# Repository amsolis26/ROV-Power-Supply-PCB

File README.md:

# ROV Power Supply PCB

## Problem
A common laptop power supply provides a much higher voltage than what the electronics in my ROV are rated for. To solve this issue, I needed to design a PCB that can fit into the 3-Inch Diameter Housing of my ROV to safely step down the voltage and power my onboard electronics.

## Approach
- Select DC/DC converter suited for the voltage conversion **(48V to 8V)** I need to power the ROV
- Design a schematic & PCB Layout using KiCAD
- Send out files for PCB manufacturing
- Order & Solder components together
- Use Desk Power supply to test if the output meets desired Voltage

## Results
The PCB delivers an output **~8V**, successfully powering onboard electronics.

## Tools
- **KiCAD** (Schematic & PCB Design)
- **PCB Way** (PCB Manufacturing)
- **DigiKey** (Part Lookup & Ordering)

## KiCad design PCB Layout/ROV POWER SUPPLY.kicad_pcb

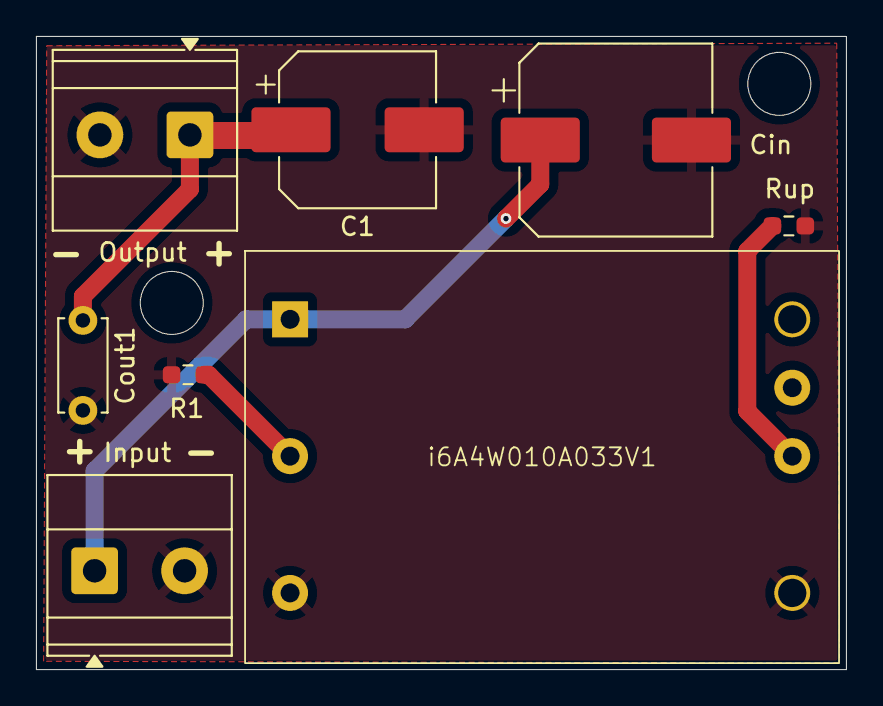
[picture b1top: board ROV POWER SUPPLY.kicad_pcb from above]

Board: 2 copper layers, 45.0 x 35.2 mm, 8 parts (0 on the bottom side), 5 nets.

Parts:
C1: 100uF; CP_Elec_8x10.5
Cin: 100uF; CP_Elec_10x12.5
Cout1: 0.1uF; C_Disc_D5.0mm_W2.5mm_P5.00mm
Input: 48V; TerminalBlock_Phoenix_MKDS-1,5-2_1x02_P5.00mm_Horizontal
Output: 8V; TerminalBlock_Phoenix_MKDS-1,5-2_1x02_P5.00mm_Horizontal
R1: 330; R_0603_1608Metric_Pad0.98x0.95mm_HandSolder
Rup: 4.3k; R_0603_1608Metric_Pad0.98x0.95mm_HandSolder
i6A4W010A033V1: DC/DC; DCDC_3.3V-40V_250W_Power_Module_Series_285-2670-ND_I6A4W010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

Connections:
8V: C1.1, Cout1.1, Output.1, i6A4W010A033V1.7 (SENSE(+)), i6A4W010A033V1.8 (Vout(+))
Earth: C1.2, Cin.2, Cout1.2, Input.2, Output.2, R1.2, Rup.2, i6A4W010A033V1.3 (Vin(-)), i6A4W010A033V1.4 (Vout(-))
unnamed: Cin.1, Input.1, i6A4W010A033V1.1 (Vin(+))
unnamed: R1.1, i6A4W010A033V1.2 (ON/OFF)
unnamed: Rup.1, i6A4W010A033V1.6 (TRIM)
